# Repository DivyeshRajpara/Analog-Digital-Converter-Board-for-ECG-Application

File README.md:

# Analog-Digital-Converter-Board-for-ECG-Application
This project involves the development of an analog-digital converter (ADC) board designed for ECG (electrocardiogram) applications using KiCad. The board interfaces with an ESP32-S3 microcontroller, which is programmed to handle data transmission to a data sink.

components
Circuit board: Schematics and PCB layout files for the ADC board.
ESP32-S3 Firmware: Code for configuring and managing data transmission from the ESP32-S3 microcontroller.
Documentation: Detailed instructions for assembling the hardware and setting up the software environment.

features
ECG Signal Acquisition: Accurate acquisition of ECG signals through the designed ADC board.
KiCAD Design: Complete PCB design using KiCad, including schematics and layout.
ESP32-S3 Integration: Programming of ESP32-S3 for efficient data processing and transmission.
Wireless Data Transmission: Real-time transmission of ECG data to a remote data sink for analysis and storage.

/1a2f7fef-0d9a-47c2-81c5-819c6184944a)

om/user-attachments/assets/370c4dd7-03d3-401c-867e-ba3244433589)

om/user-attachments/assets/a84ef1b4-a10b-4781-94ae-7ec4066e7fd7)

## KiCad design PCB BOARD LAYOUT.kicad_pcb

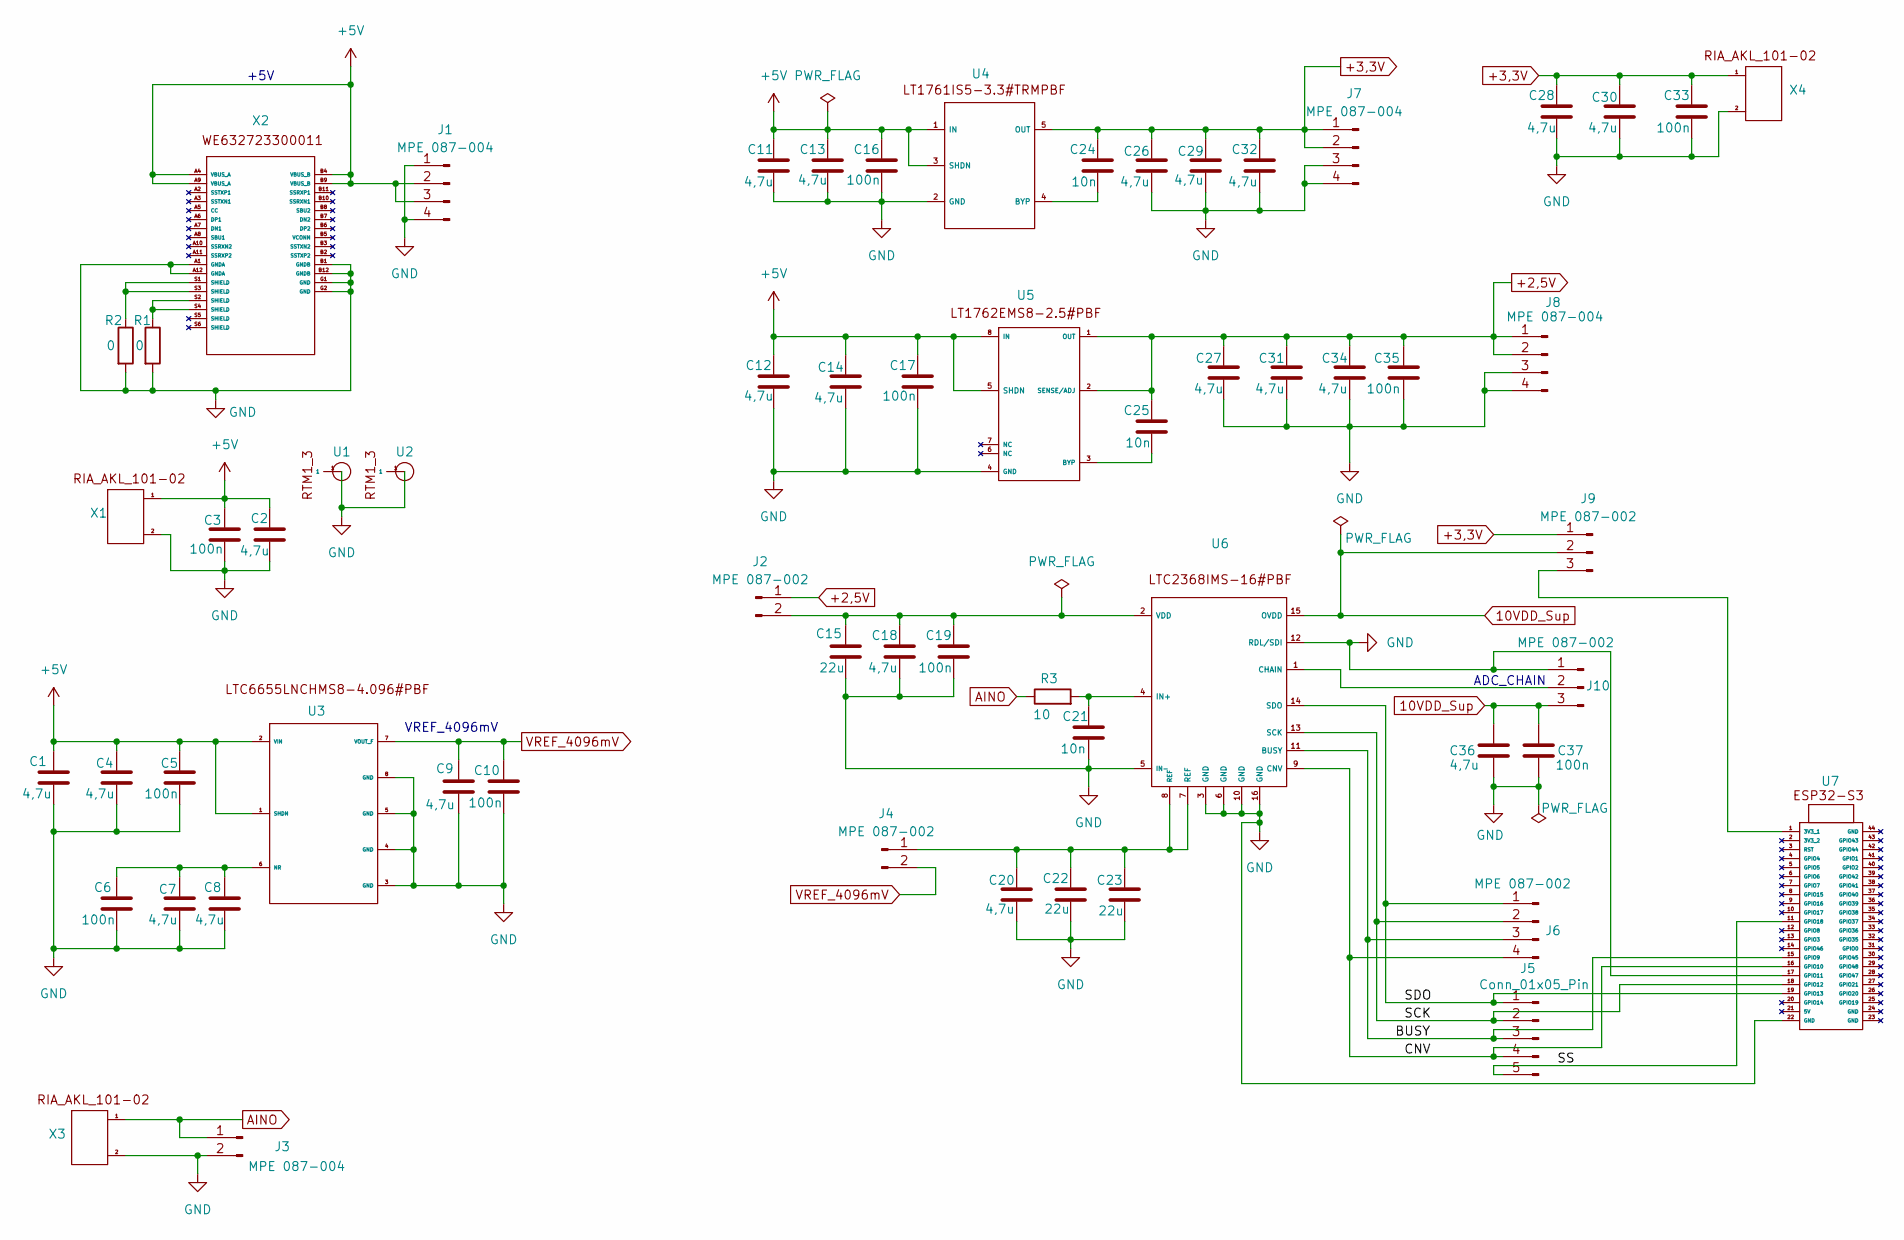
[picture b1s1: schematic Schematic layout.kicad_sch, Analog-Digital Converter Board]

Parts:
C1, C2, C4, C7, C8, C9, C11, C12, C13, C14, C18, C20, C26, C27, C28, C29, C30, C31, C32, C34, C36: 4,7u; C_0603_1608Metric_Pad1.08x0.95mm_HandSolder
C3, C5, C6, C10, C16, C17, C19, C33, C35, C37: 100n; C_0603_1608Metric_Pad1.08x0.95mm_HandSolder
C15, C22, C23: 22u; C_0805_2012Metric_Pad1.18x1.45mm_HandSolder
C21, C24, C25: 10n; C_0603_1608Metric_Pad1.08x0.95mm_HandSolder
J1, J7, J8: MPE 087-004; PinHeader_1x04_P2.54mm_Vertical
J2, J4: MPE 087-002; PinHeader_1x02_P2.54mm_Vertical
J3: MPE 087-004; PinHeader_1x02_P2.54mm_Vertical
J5: Conn_01x05_Pin; PinHeader_1x05_P2.54mm_Vertical
J6: MPE 087-002; PinHeader_1x04_P2.54mm_Vertical
J9, J10: MPE 087-002; PinHeader_1x03_P2.54mm_Vertical
R1, R2: 0; R_0402_1005Metric_Pad0.72x0.64mm_HandSolder
R3: 10; R_0603_1608Metric_Pad0.98x0.95mm_HandSolder
U1, U2: RTM1_3
U3: LTC6655LNCHMS8.4.096#PBF
U4: LT1761IS5-3.3TRMPBF
U5: LT1762EMS8-2.5#PBF
U6: LTC2368IMS-16PBF
U7: ESP32-S3
X1, X3, X4: RIA_AKL_101-02
X2: WE632723300011

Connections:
10VDD_Sup: C36.1, C37.1, J9.2, J10.3, U6.15 (OVDD)
+2,5V: C25.1, C27.1, C31.1, C34.1, C35.1, J2.1, J8.1, J8.2, U5.1 (OUT), U5.2 (SENSE/ADJ)
+3,3V: C24.1, C26.1, C28.1, C29.1, C30.1, C32.1, C33.1, J7.1, J7.2, J9.1, U4.5 (OUT), X4.1
+5V: C1.1, C2.1, C3.1, C4.1, C5.1, C11.1, C12.1, C13.1, C14.1, C16.1, C17.1, J1.2, J1.3, U3.1 (SHDN), U3.2 (VIN), U4.1 (IN), U4.3 (SHDN), U5.5 (SHDN), U5.8 (IN), X1.1, X2.A4 (VBUS_A), X2.A9 (VBUS_A), X2.B4 (VBUS_B), X2.B9 (VBUS_B)
/BUSY: J5.3, J6.3, U6.11 (BUSY), U7.15 (GPIO9)
/CNV: J5.4, J6.4, U6.9 (CNV), U7.16 (GPIO10)
/SCK: J5.2, J6.2, U6.13 (SCK), U7.18 (GPIO12)
/SDO: J5.1, J6.1, U6.14 (SDO), U7.19 (GPIO13)
/SS: J5.5, U7.11 (GPIO18)
AINO: J3.1, R3.1, X3.1
GND: C1.2, C2.2, C3.2, C4.2, C5.2, C6.2, C7.2, C8.2, C9.2, C10.2, C11.2, C12.2, C13.2, C14.2, C15.2, C16.2, C17.2, C18.2, C19.2, C20.2, C21.2, C22.2, C23.2, C26.2, C27.2, C28.2, C29.2, C30.2, C31.2, C32.2, C33.2, C34.2, C35.2, C36.2, C37.2, J1.1, J1.4, J3.2, J7.3, J7.4, J8.3, J8.4, J10.1, R1.2, R2.2, U1.1, U2.1, U3.3 (GND), U3.4 (GND), U3.5 (GND), U3.8 (GND), U4.2 (GND), U5.4 (GND), U6.3 (GND), U6.5 (IN-), U6.6 (GND), U6.10 (GND), U6.12 (RDL/SDI), U6.16 (GND), U7.17 (GPIO11), U7.22 (GND), X1.2, X2.A1 (GNDA), X2.A12 (GNDA), X2.B1 (GNDB), X2.B12 (GNDB), X2.G1 (GND), X2.G2 (GND), X3.2, X4.2
unnamed: C15.1, C18.1, C19.1, J2.2, U6.2 (VDD)
unnamed: C20.1, C22.1, C23.1, J4.1, U6.7 (REF), U6.8 (REF)
unnamed: J9.3, U7.1 (3V3_1)
unnamed: J10.2, U6.1 (CHAIN)
unnamed: R1.1, X2.S2 (SHIELD), X2.S4 (SHIELD)
unnamed: R2.1, X2.S1 (SHIELD), X2.S3 (SHIELD)
unnamed: C6.1, C7.1, C8.1, U3.6 (NR)
unnamed: C24.2, U4.4 (BYP)
unnamed: C25.2, U5.3 (BYP)
unnamed: C21.1, R3.2, U6.4 (IN+)
VREF_4096mV: C9.1, C10.1, J4.2, U3.7 (VOUT_F)

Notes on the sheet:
ADC_CHAIN
+5V
VREF_4096mV

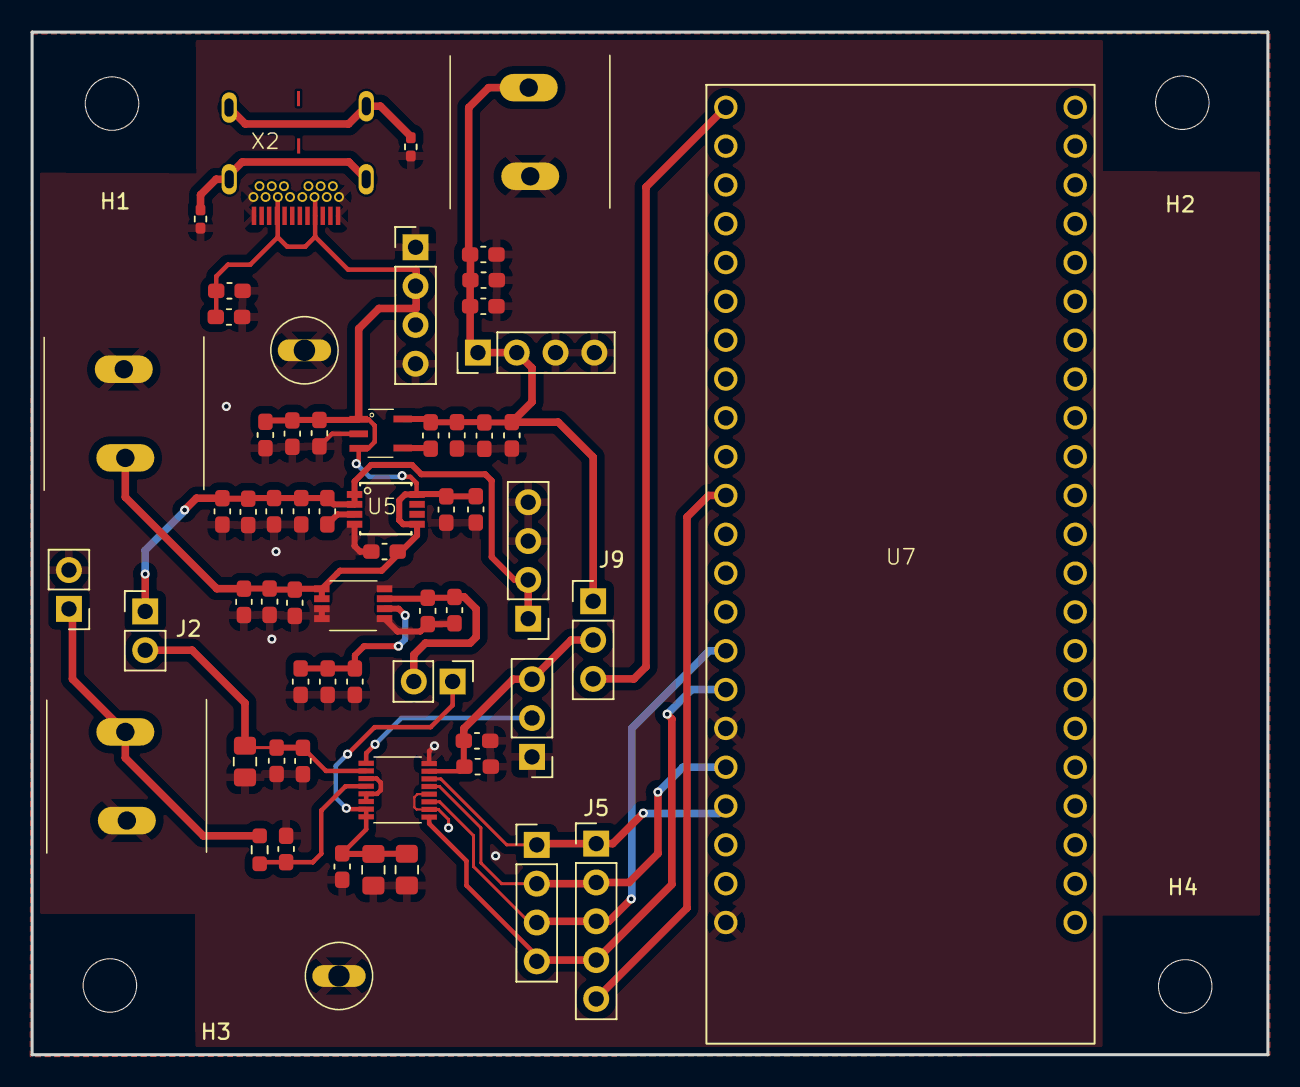
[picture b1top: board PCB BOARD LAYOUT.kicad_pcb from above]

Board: 2 copper layers, 80.9 x 66.9 mm, 65 parts (0 on the bottom side), 22 nets.

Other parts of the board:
H1, H2, H3, H4: MountingHole_3.5mm
